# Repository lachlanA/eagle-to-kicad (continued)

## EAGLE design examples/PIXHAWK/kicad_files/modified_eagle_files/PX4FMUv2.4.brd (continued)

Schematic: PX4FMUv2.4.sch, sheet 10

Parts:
C1001: 10u/25V; 0805-CAP; PARTNO CL21A106KAYNNNE
C1002: 10n; 0402-CAP; PARTNO CC0402KRX7R7BB103
C1003: 1u0; 0603-CAP; PARTNO CC0603ZRY5V7BB105
C1004: 10u; 0603-CAP; PARTNO CC0603ZRY5V7BB105
C1005: 0u1F; 0402-CAP; PARTNO CC0402ZRY5V7BB104
C1008: 2u2; 0402-CAP; PARTNO CC0603ZRY5V7BB105
D1001: PMEG2005CT; SOT23-3; PARTNO PMEG2005CT
F1001: 0ZCA0035FF2G; PTC-1206; PARTNO 0ZCA0035FF2G
R1001: 100K; 0402-RES; PARTNO RC0402FR-07100KL
R1002: 10K; 0402-RES; PARTNO RC0402FR-0710KL
U1001: BQ24313; QFN8-DSG; PARTNO BQ24313DSGT
U1002: MIC5332; MLF-8-EPAD; PARTNO MIC5332-SSYMT

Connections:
GND: C1001.P$2 (2), C1002.P$2 (2), C1003.P$2 (2), C1004.P$2 (2), C1005.P$2 (2), C1008.P$2 (2), R1001.P$1 (1), R1002.P$1 (1), U1001.2 (VSS), U1001.5 (!CE), U1001.6 (VBAT), U1001.GND (VSS), U1001.P$2 (VSS), U1001.P$3 (VSS), U1002.2 (GND), U1002.GND; also elsewhere on the board
IO-!RESET: U1002.3 (POR2); also elsewhere on the board
IO-!VDD_SERVO_IN_FAULT: U1001.4 (!FAULT); also elsewhere on the board
IO-VDD_3V3: C1003.P$1 (1), C1004.P$1 (1), U1002.7 (VOUT2); also elsewhere on the board
IO-VDD_5V5: C1001.P$1 (1), C1005.P$1 (1), D1001.3 (CC), U1002.1 (VIN), U1002.4 (EN2); also elsewhere on the board
unnamed: D1001.2 (A2), U1001.8 (OUT)
unnamed: R1001.P$2 (2), U1001.7 (ILIM)
unnamed: D1001.1 (A1), F1001.2
unnamed: C1002.P$1 (1), U1002.6 (CSET)
VDD_3V3_SPEKTRUM: C1008.P$1 (1), U1002.8 (VOUT1); also elsewhere on the board
VDD_3V3_SPEKTRUM_EN: R1002.P$2 (2), U1002.5 (EN1); also elsewhere on the board
VDD_5V_IN: F1001.1; also elsewhere on the board
VDD_SERVO_IN: U1001.1 (IN); also elsewhere on the board

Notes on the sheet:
Dual supply from servo rail and FMU 5V rail
Current limit = 25 / Rilim (current in A, R in kOhms) 100K = 250mA
IO Power Supply
Reset output 1s / uF 10n = 10ms delay from power good to reset de-asserted.
Output voltage limited to 5.5V for input voltages up to 10.5V; output switches off at higher input voltages.

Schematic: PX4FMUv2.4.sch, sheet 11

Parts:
C1101, C1102, C1103: 22u/25V; 0805-CAP; PARTNO CL21A226MAQNNNE
C1104: 100u; 1206-CAP; PARTNO C3216X5R1A107M160AC
C1105, C1106, C1107: 0u1; 0402-CAP; PARTNO CC0402ZRY5V7BB104
C1108, C1109, C1110: 1000p/25V; 0402-CAP; PARTNO GRM1555C1E102JA01D
J601: DF13C-6P-1.25V; PARTNO DF13C-6P-1.25V(20)
L1101, L1102: KNH16C104DA5TS; KYOCERA-KNH16-DA; PARTNO KNH16C104DA5TS
R1101, R1102: 10K/0.1%; 0402-RES; PARTNO ERA-2AEB103X
R1103, R1104: 1M; 0402-RES; PARTNO RC0402FR-071ML
R1105, R1109, R1112: 453K; 0402-RES; PARTNO RMCF0402FT453K
R1106, R1110, R1113: 56K; 0402-RES; PARTNO ERA-2AEB563X
R1107, R1111, R1114: 105K; 0402-RES; PARTNO ERJ-2RKF1053X
R1115: 0R; 0402-RES; PARTNO ERJ-2GE0R00X
RN1101: 1M; EXB28V; PARTNO EXB-28V105JX
U1101: LTC4417; MO-220; PARTNO LTC4417IUF#PBF
U1102, U1103, U1104: NTHD4102PT1G; 1206-8; PARTNO NTHD4102PT1G

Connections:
!VBUS_VALID: RN1101.2 (1), U1101.P$9 (!VALID3); also elsewhere on the board
!VDD_BRICK_VALID: RN1101.4 (1), U1101.P$7 (!VALID1); also elsewhere on the board
!VDD_SERVO_VALID: RN1101.3 (1), U1101.P$8 (!VALID2); also elsewhere on the board
BATT_CURRENT_SENS: R1101.P$1 (1); also elsewhere on the board
BATT_CURRENT_SENS_PROT: J601.3, L1101.P$1, R1104.P$1 (1)
BATT_VOLTAGE_SENS: R1102.P$1 (1); also elsewhere on the board
BATT_VOLTAGE_SENS_PROT: J601.4, L1102.P$1, R1103.P$1 (1)
GND: C1101.P$2 (2), C1102.P$2 (2), C1103.P$2 (2), C1104.P$2 (2), C1105.P$2 (2), C1106.P$2 (2), C1107.P$2 (2), C1108.P$2 (2), C1109.P$2 (2), C1110.P$2 (2), J601.5, J601.6, L1101.P$3, L1101.P$4, L1101.P$5, L1102.P$3, L1102.P$4, L1102.P$5, R1103.P$2 (2), R1104.P$2 (2), R1107.P$2 (2), R1111.P$2 (2), R1114.P$2 (2), R1115.P$1 (1), U1101.P$10 (GND), U1101.P$25 (GND); also elsewhere on the board
unnamed: C1108.P$1 (1), R1105.P$2 (2), R1106.P$1 (1), U1101.P$1 (UV1)
unnamed: R1106.P$2 (2), R1107.P$1 (1), U1101.P$2 (OV1)
unnamed: C1109.P$1 (1), R1109.P$2 (2), R1110.P$1 (1), U1101.P$3 (UV2)
unnamed: R1110.P$2 (2), R1111.P$1 (1), U1101.P$4 (OV2)
unnamed: R1113.P$2 (2), R1114.P$1 (1), U1101.P$6 (OV3)
unnamed: C1110.P$1 (1), R1112.P$2 (2), R1113.P$1 (1), U1101.P$5 (UV3)
unnamed: C1105.P$1 (1), U1101.P$18 (VS1), U1102.P$1 (S), U1102.P$3 (S)
unnamed: L1102.P$2, R1102.P$2 (2)
unnamed: L1101.P$2, R1101.P$2 (2)
unnamed: R1115.P$2 (2), U1101.P$24 (HYS)
unnamed: C1106.P$1 (1), U1101.P$16 (VS2), U1103.P$1 (S), U1103.P$3 (S)
unnamed: C1107.P$1 (1), U1101.P$14 (VS3), U1104.P$1 (S), U1104.P$3 (S)
unnamed: U1101.P$13 (G3), U1104.P$2 (G), U1104.P$4 (G)
unnamed: U1101.P$15 (G2), U1103.P$2 (G), U1103.P$4 (G)
unnamed: U1101.P$17 (G1), U1102.P$2 (G), U1102.P$4 (G)
VBUS: C1103.P$1 (1), R1112.P$1 (1), U1101.P$19 (V3), U1104.P$7 (D), U1104.P$8 (D); also elsewhere on the board
VDD_5V_BRICK: C1101.P$1 (1), J601.1, J601.2, R1105.P$1 (1), U1101.P$21 (V1), U1102.P$7 (D), U1102.P$8 (D); also elsewhere on the board
VDD_5V_IN: C1104.P$1 (1), RN1101.5 (2), RN1101.6 (2), RN1101.7 (2), U1101.P$12 (VOUT), U1102.P$5 (D), U1102.P$6 (D), U1103.P$5 (D), U1103.P$6 (D), U1104.P$5 (D), U1104.P$6 (D); also elsewhere on the board
VDD_SERVO: C1102.P$1 (1), R1109.P$1 (1), U1101.P$20 (V2), U1103.P$7 (D), U1103.P$8 (D); also elsewhere on the board

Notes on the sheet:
Power source selector
Resistors picked so that undervoltage lockout starts at 4.0V and overvoltage lockout at 5.75V. Use 1% or better accuracy!
POWER PATH CONTROLLER: Does enable output if valid for continous 256 ms

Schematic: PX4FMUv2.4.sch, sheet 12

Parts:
!VBUS_VALID1116: PAD.04; PAD.04X.04; PARTNO *
!VDD_BRICK_VALID1116: PAD.04; PAD.04X.04; PARTNO *
!VDD_SERVO_VALID1116: PAD.04; PAD.04X.04; PARTNO *
ADC_PR1116: PAD.04; PAD.04X.04; PARTNO *
CAN_H1116: PAD.04; PAD.04X.04; PARTNO *
CAN_L1116: PAD.04; PAD.04X.04; PARTNO *
FMU-BOOT1101: PAD.04; PAD.04X.04; PARTNO *
GND1116, GND.1116: PAD.04; PAD.04X.04; PARTNO *
IO-BOOT1101: PAD.04; PAD.04X.04; PARTNO *
JP1, JP2: FIDUCIAL1.5X3; FIDUCIAL-1.5X3; PARTNO *
M3_MOUNT1101, M3_MOUNT1102, M3_MOUNT1103, M3_MOUNT1104: MOUNT-HOLE3.1MM; MOUNT-HOLE3.1; PARTNO *
OSHW_LOGO1116: OSHW-LOGOS; OSHW-LOGO-S; PARTNO *
S1RX1116, S1TX1116, S2RX1116, S2TX1116, S3RX1116, S3TX1116, S4RX1116, S4TX1116, S5_RX1116, S5_TX1116: PAD.04; PAD.04X.04; PARTNO *
VBUS1116: PAD.04; PAD.04X.04; PARTNO *
VDDA_3V1101: PAD.04; PAD.04X.04; PARTNO *
VDD_3V1101, VDD_5V_BRICK1116, VDD_5V_IN1116: PAD.04; PAD.04X.04; PARTNO *
VDD_SERVO1116: PAD.04; PAD.04X.04; PARTNO *
VP_0, VP_1, VP_2, VP_3, VP_33, VP_34, VP_35, VP_41, VP_42, VP_43, VP_51, VP_52, VP_53, VP_54, VP_55, VP_56, VP_57, VP_58, VP_59, VP_60, VP_61: VPDEV0; VPAC0
VP_4, VP_5, VP_6, VP_7, VP_8, VP_9, VP_10, VP_11, VP_12, VP_13, VP_14, VP_15, VP_16, VP_17, VP_18, VP_19, VP_20, VP_21, VP_22, VP_23, VP_24, VP_25, VP_26, VP_27, VP_28, VP_29, VP_30, VP_31, VP_32, VP_36, VP_37, VP_39, VP_40, VP_44, VP_45, VP_46, VP_47, VP_48, VP_49, VP_50: VPDEV1; VPAC1
VP_38: VPDEV2; VPAC2

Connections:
!VBUS_VALID: !VBUS_VALID1116.P$1; also elsewhere on the board
!VDD_BRICK_VALID: !VDD_BRICK_VALID1116.P$1; also elsewhere on the board
!VDD_SERVO_VALID: !VDD_SERVO_VALID1116.P$1; also elsewhere on the board
CAN_H: CAN_H1116.P$1; also elsewhere on the board
CAN_L: CAN_L1116.P$1; also elsewhere on the board
FMU-BOOT0: FMU-BOOT1101.P$1; also elsewhere on the board
FMU-VDD_3V3: VDD_3V1101.P$1; also elsewhere on the board
GND: GND1116.P$1, GND.1116.P$1, VP_0.VP, VP_1.VP, VP_2.VP, VP_3.VP, VP_4.VP, VP_5.VP, VP_6.VP, VP_7.VP, VP_8.VP, VP_9.VP, VP_10.VP, VP_11.VP, VP_12.VP, VP_13.VP, VP_14.VP, VP_15.VP, VP_16.VP, VP_17.VP, VP_18.VP, VP_19.VP, VP_20.VP, VP_21.VP, VP_22.VP, VP_23.VP, VP_24.VP, VP_25.VP, VP_26.VP, VP_27.VP, VP_28.VP, VP_29.VP, VP_30.VP; also elsewhere on the board
IO-BOOT0: IO-BOOT1101.P$1; also elsewhere on the board
IO-VDD_3V3: VP_31.VP, VP_32.VP; also elsewhere on the board
PRESSURE_SENS_IN: ADC_PR1116.P$1; also elsewhere on the board
SERIAL1_RX: S1RX1116.P$1; also elsewhere on the board
SERIAL1_TX: S1TX1116.P$1; also elsewhere on the board
SERIAL2_RX: S2RX1116.P$1; also elsewhere on the board
SERIAL2_TX: S2TX1116.P$1; also elsewhere on the board
SERIAL3_RX: S3RX1116.P$1; also elsewhere on the board
SERIAL3_TX: S3TX1116.P$1; also elsewhere on the board
SERIAL4_RX: S4RX1116.P$1; also elsewhere on the board
SERIAL4_TX: S4TX1116.P$1; also elsewhere on the board
SERIAL5_RX: S5_RX1116.P$1; also elsewhere on the board
SERIAL5_TX: S5_TX1116.P$1; also elsewhere on the board
VBUS: VBUS1116.P$1, VP_33.VP, VP_34.VP, VP_35.VP; also elsewhere on the board
VDD_3V3_SENSORS: VDDA_3V1101.P$1, VP_36.VP, VP_37.VP; also elsewhere on the board
VDD_5V_BRICK: VDD_5V_BRICK1116.P$1, VP_38.VP, VP_39.VP, VP_40.VP; also elsewhere on the board
VDD_5V_IN: VDD_5V_IN1116.P$1, VP_41.VP, VP_42.VP, VP_43.VP, VP_44.VP, VP_45.VP, VP_46.VP, VP_47.VP, VP_48.VP, VP_49.VP, VP_50.VP, VP_51.VP, VP_52.VP, VP_53.VP; also elsewhere on the board
VDD_5V_PERIPH: VP_54.VP, VP_55.VP, VP_56.VP, VP_57.VP, VP_58.VP; also elsewhere on the board
VDD_SERVO: VDD_SERVO1116.P$1, VP_59.VP, VP_60.VP, VP_61.VP; also elsewhere on the board

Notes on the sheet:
Mounting holes to suit M3 fastener
and Richco R908 series spacer.
Use R908-5 spacers to stack with
other PX4 series boards (7.95 mm).
Production Testing Pads
Test and Fiducials
Minimum drill: 0.3 mm
Minimum trace width (use mm for traces): 0.15 mm
Minimum copper distance (all signals): 0.15 mm
Dimension / hole minimum distance: 0.2 mm
Layout grid: 4 mil, part grid: 4 mil. Dimensions / hole positions: 0.5 mm
Board: FR4 black, 1.0 mm. Solder stop on vias < 0.6 mm.
Signoff rules: Footprint checked, pinmap checked, schematic checked, cross-references to other pages checked.
Routing: 1: general/escape 2: ground 3: horizontal 4: vertical 5: power 6: general/escape
Fiducials for machine vision alignment.
Parts: Resistors: 0402 / 1% unless specified otherwise Capacitors: 0402 to 1206, ceramic, voltage rating: 10V unless specified

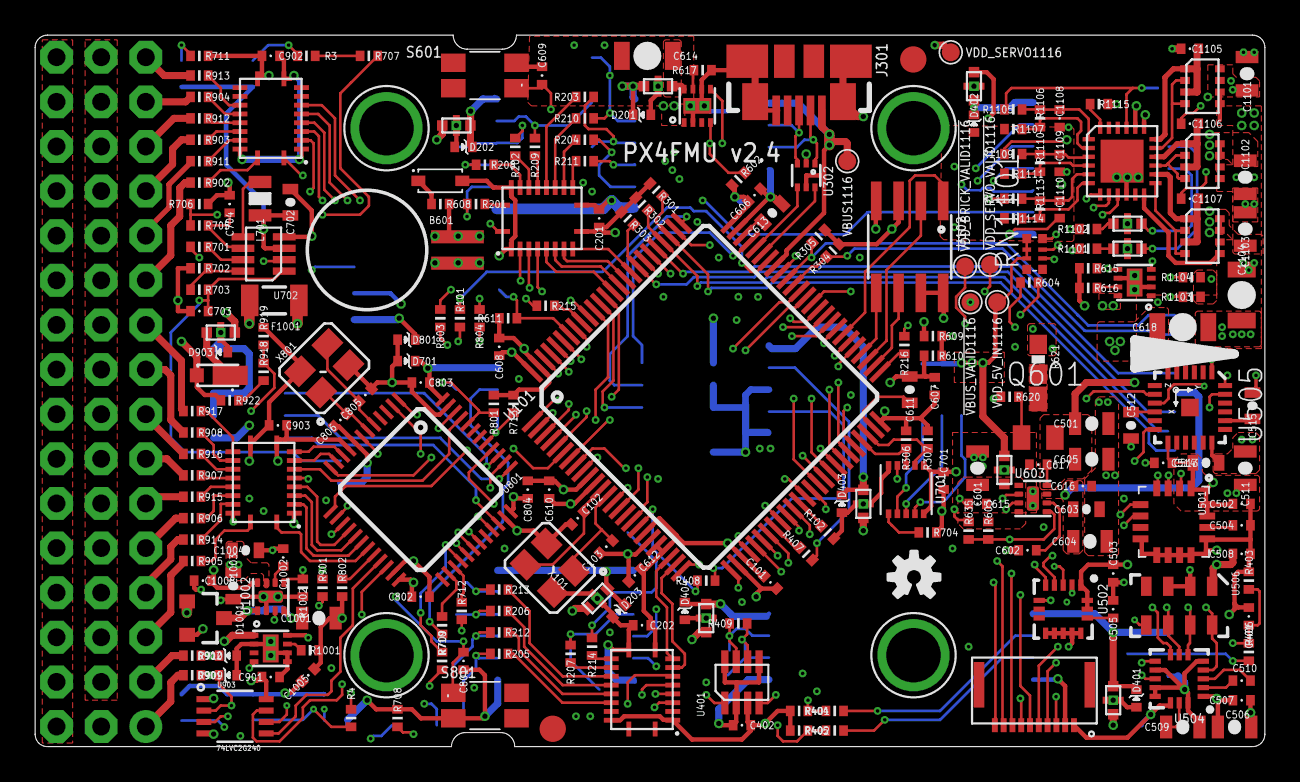
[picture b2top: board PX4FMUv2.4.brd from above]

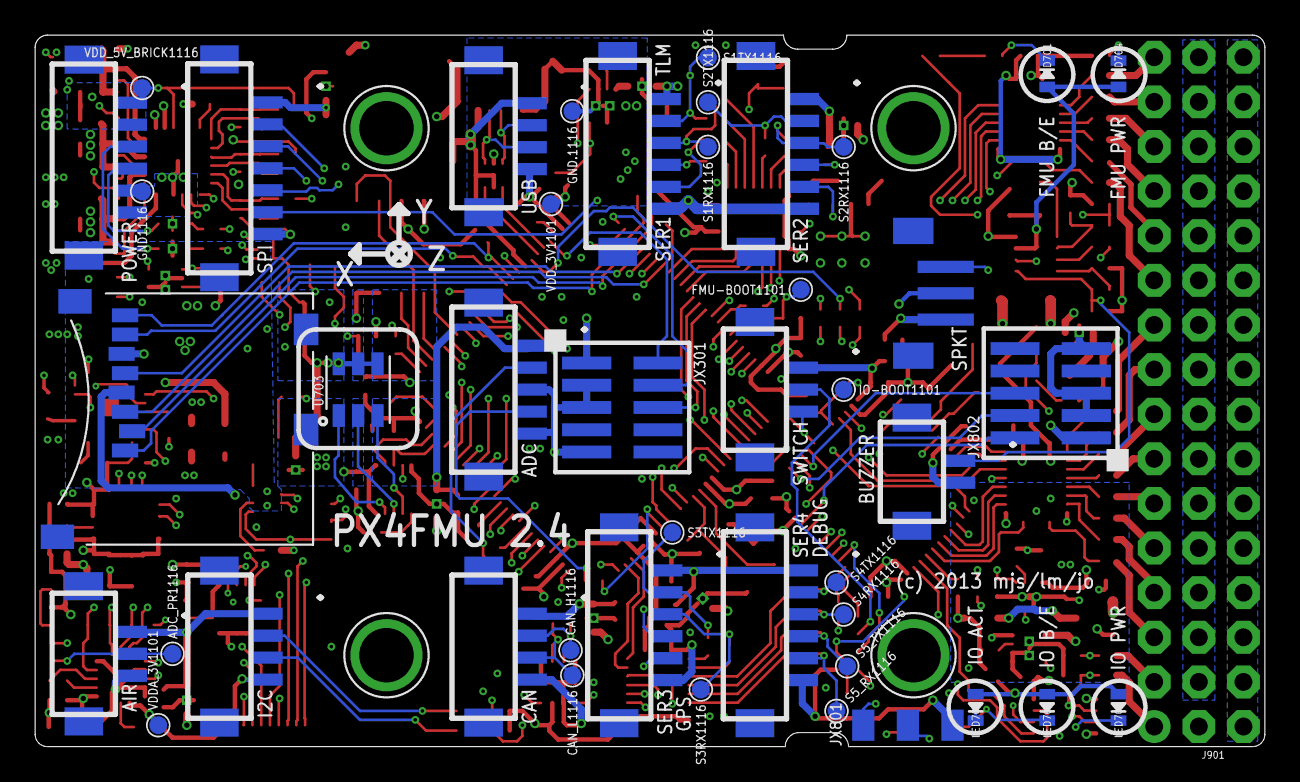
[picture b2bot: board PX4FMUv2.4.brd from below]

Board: 6 copper layers, 70.0 x 40.5 mm, 354 parts (45 on the bottom side), 262 nets.

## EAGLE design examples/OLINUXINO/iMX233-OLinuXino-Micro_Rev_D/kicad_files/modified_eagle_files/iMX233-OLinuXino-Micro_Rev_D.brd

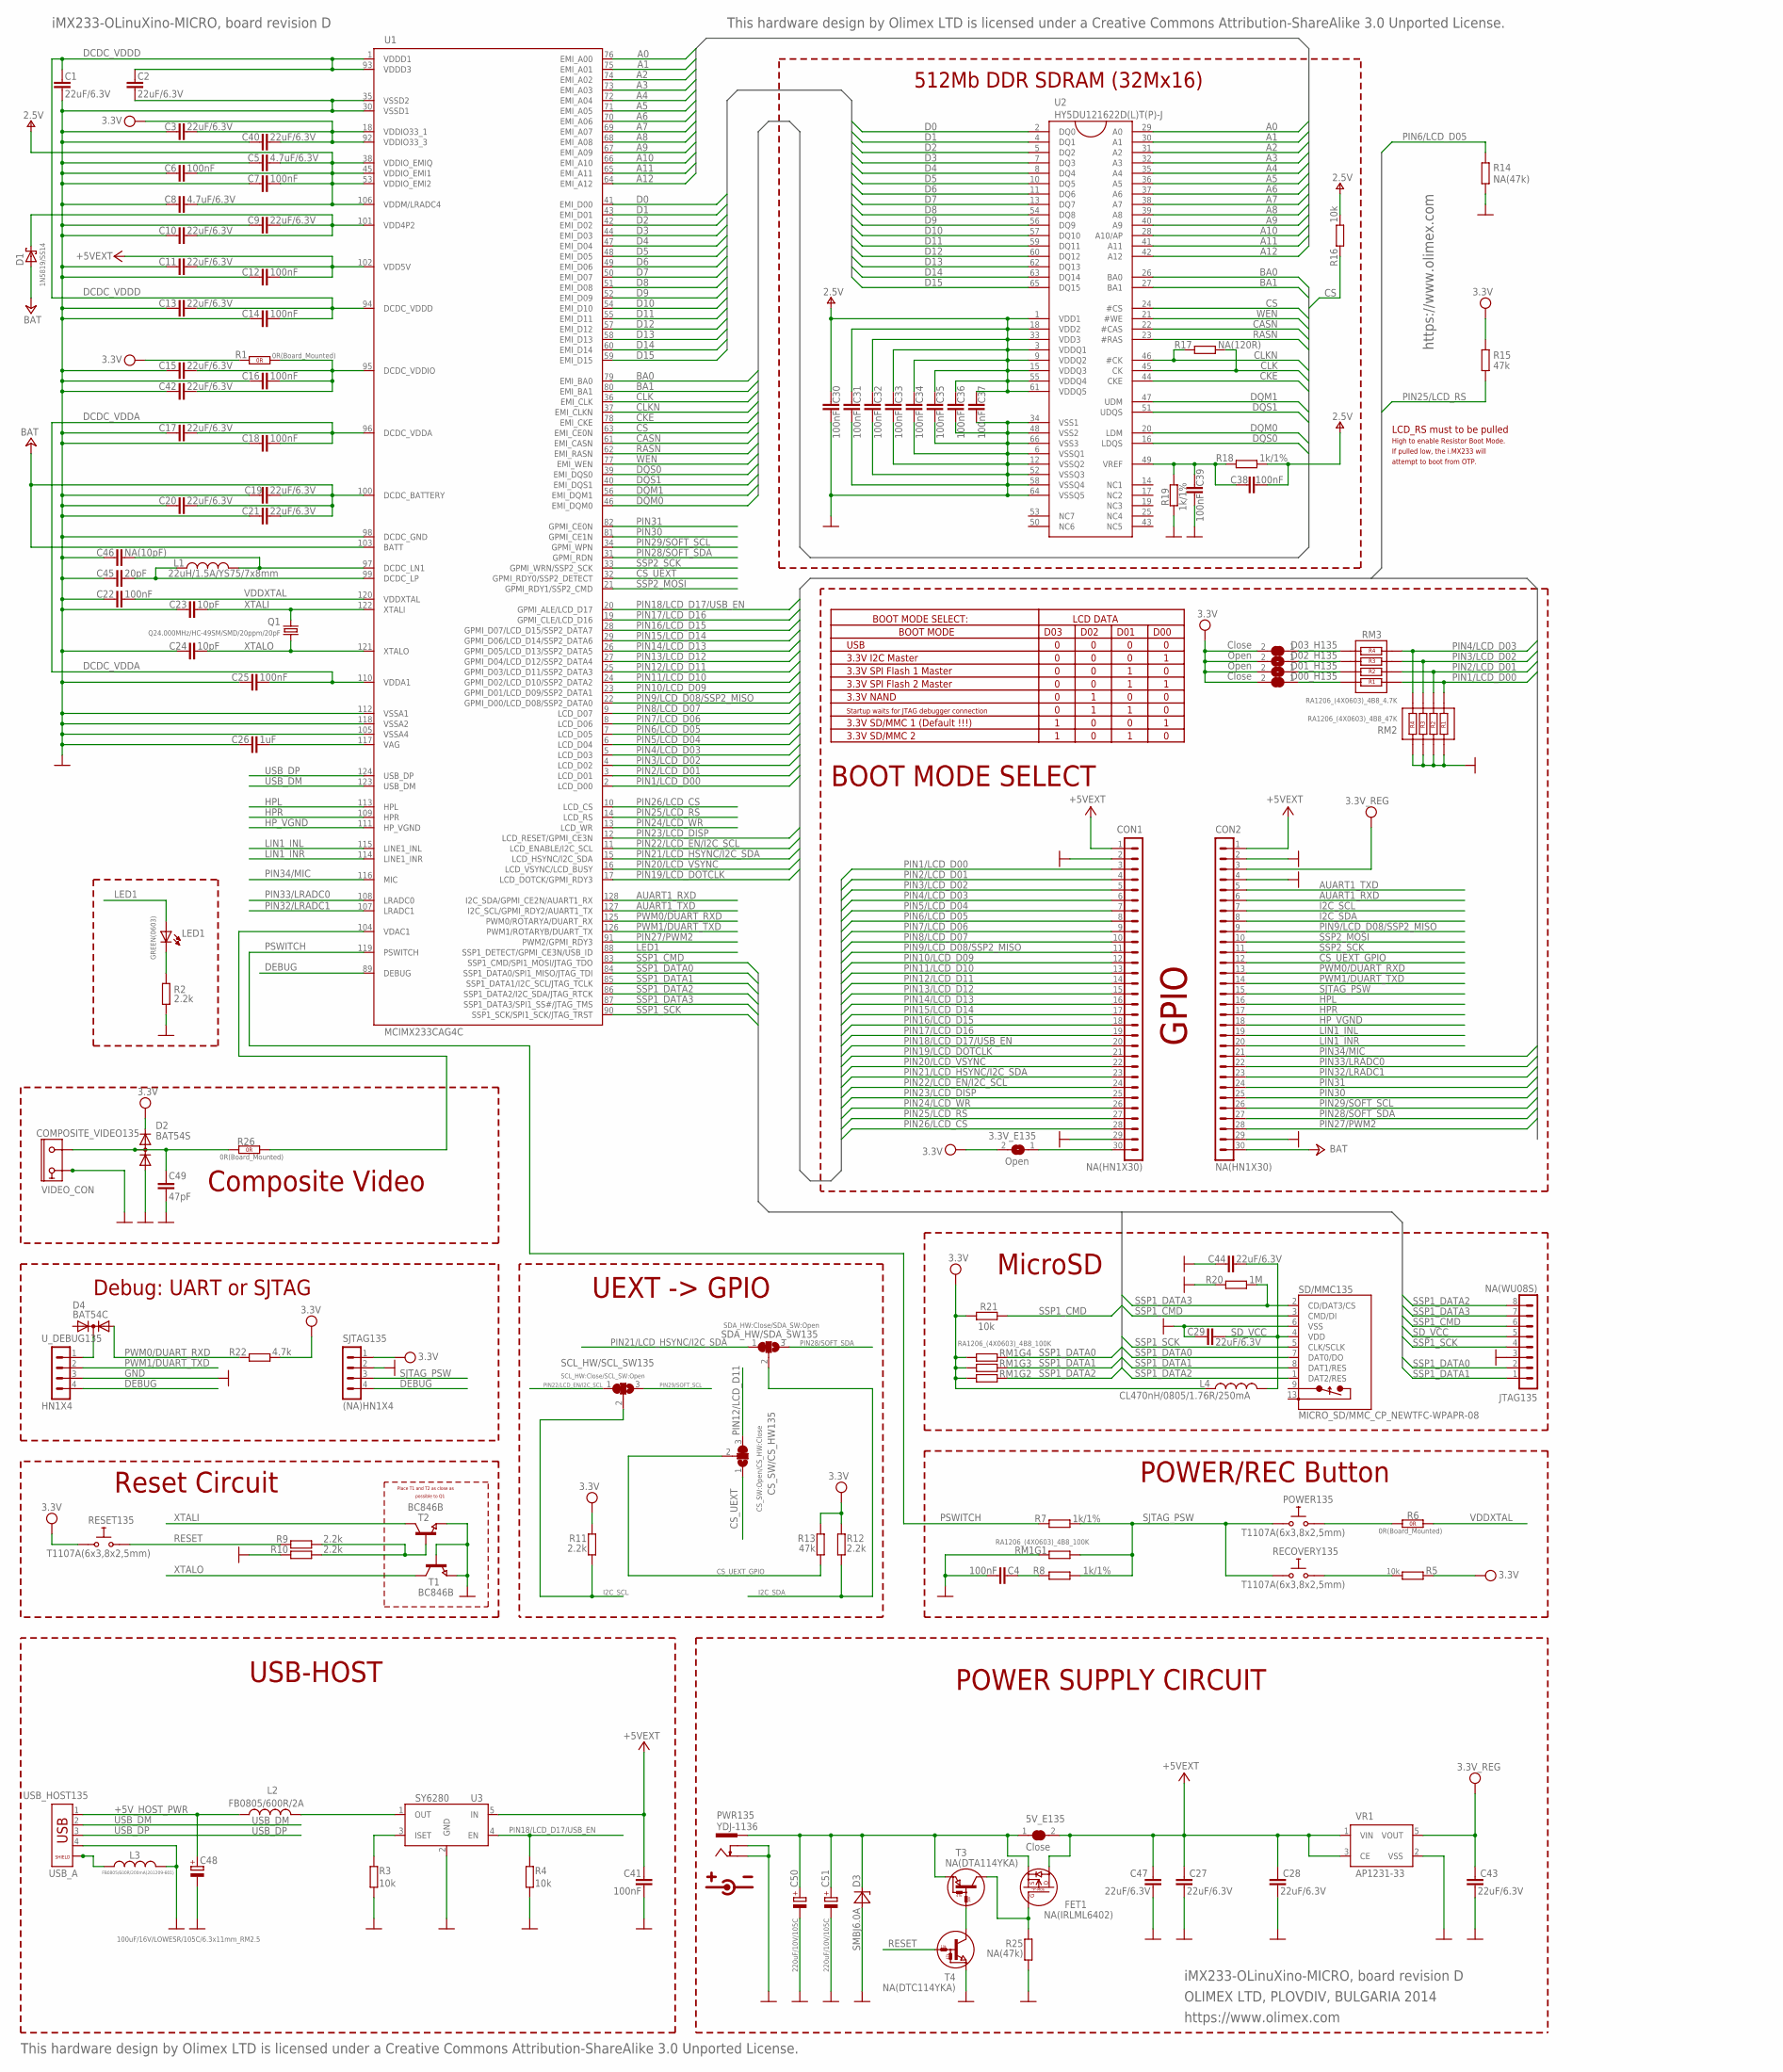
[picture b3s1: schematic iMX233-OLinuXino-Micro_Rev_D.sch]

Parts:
3.3V_E135: Open; SJ_1_SMALLER
5V_E135: Close; SJ-CLOSE
C1, C2, C9, C10, C11, C13, C15, C17, C19, C20, C21, C27, C28, C29, C40, C42, C43, C44, C47: 22uF/6.3V; C0603_DWS
C3: 22uF/6.3V; C1206
C4, C6, C7, C12, C14, C16, C18, C22, C25, C30, C31, C32, C33, C34, C35, C36, C37, C38, C39, C41: 100nF; C0603_DWS
C5, C8: 4.7uF/6.3V; C0603_DWS
C23, C24: 10pF; C0603_DWS
C26: 1uF; C0603_DWS
C45: 20pF; C0603_DWS
C46: NA(10pF); C0603_DWS
C48: 100uF/16V/LOWESR/105C/6.3x11mm_RM2.5; E2,5-6,3
C49: 47pF; C0603_DWS
C50, C51: 220uF/10V/105C; E2,5-6,3
COMPOSITE_VIDEO135: VIDEO_CON; VIDEO_CINCH
CON1, CON2: NA(HN1X30); HN1X30
CS_SW/CS_HW135: CS_SW:Open/CS_HW:Close; SJ_2_SMALL
D00_H135, D03_H135: Close; SJ_1_SMALLER
D1: 1N5819/SS14; MLL-41
D01_H135, D02_H135: Open; SJ_1_SMALLER
D2: BAT54S; SOT23C(BAT54S)
D3: SMBJ6.0A; DO214AA
D4: BAT54C; SOT23C
FET1: NA(IRLML6402); SOT23
JTAG135: NA(WU08S); WU08S
L1: 22uH/1.5A/YS75/7x8mm; L7078
L2: FB0805/600R/2A; L0805_5MIL_DWS
L3: FB0805/600R/200mA(201209-601); L0805_5MIL_DWS
L4: CL470nH/0805/1.76R/250mA; L0805_5MIL_DWS
LED1: GREEN(0603); LED-0603
POWER135: T1107A(6x3,8x2,5mm); SW-TAKT_6X3.5_SMD
PWR135: YDJ-1136; PWR_JACK_UNI_MILLING
Q1: Q24.000MHz/HC-49SM/SMD/20ppm/20pF; HC49/SMD2_THIN
R1, R6, R26: 0R(Board_Mounted); 0603_0R
R2, R9, R10, R11, R12: 2.2k; R0603_5MIL_DWS
R3, R4, R5, R16, R21: 10k; R0603_5MIL_DWS
R7, R8, R18, R19: 1k/1%; R0603_5MIL_DWS
R13, R15: 47k; R0603_5MIL_DWS
R14, R25: NA(47k); R0603_5MIL_DWS
R17: NA(120R); R0603_5MIL_DWS
R20: 1M; R0603_5MIL_DWS
R22: 4.7k; R0603_5MIL_DWS
RECOVERY135: T1107A(6x3,8x2,5mm); SW-TAKT_6X3.5_SMD
RESET135: T1107A(6x3,8x2,5mm); SW-TAKT_6X3.5_SMD
RM1: RA1206_(4X0603)_4B8_100K; R_MATRIX_4
RM2: RA1206_(4X0603)_4B8_47K; R_MATRIX_4
RM3: RA1206_(4X0603)_4B8_4.7K; R_MATRIX_4
SCL_HW/SCL_SW135: SCL_HW:Close/SCL_SW:Open; SJ_2_SMALL
SD/MMC135: MICRO_SD/MMC_CP_NEWTFC-WPAPR-08; TFC-WPAPR-08
SDA_HW/SDA_SW135: SDA_HW:Close/SDA_SW:Open; SJ_2_SMALL
SJTAG135: (NA)HN1X4; HN1X4
T1, T2: BC846B; SOT23
T3: NA(DTA114YKA); SOT-23
T4: NA(DTC114YKA); SOT-23
U1: MCIMX233CAG4C; TQFP128LD
U2: HY5DU121622D(L)T(P)-J; 66TSOP-II
U3: SY6280; SOT23-5
USB_HOST135: USB_A; USB_PN87520_HOST_PTH
U_DEBUG135: HN1X4
VR1: AP1231-33; SOT-23-5

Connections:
+5V: 5V_E135.2, C11.2, C12.2, C27.1, C28.1, C41.1, C47.1, CON1.1, CON2.1, FET1.3 (D), U1.102 (VDD5V), U3.5 (IN), VR1.1 (VIN), VR1.3 (CE)
+5V_HOST_PWR: C48.+, L2.1, USB_HOST135.1
+24V: C19.2, C20.2, C21.2, CON2.30, D1.A, U1.100 (DCDC_BATTERY), U1.103 (BATT)
A0: U1.76 (EMI_A00), U2.29 (A0)
A1: U1.75 (EMI_A01), U2.30 (A1)
A2: U1.74 (EMI_A02), U2.31 (A2)
A3: U1.73 (EMI_A03), U2.32 (A3)
A4: U1.72 (EMI_A04), U2.35 (A4)
A5: U1.71 (EMI_A05), U2.36 (A5)
A6: U1.70 (EMI_A06), U2.37 (A6)
A7: U1.69 (EMI_A07), U2.38 (A7)
A8: U1.68 (EMI_A08), U2.39 (A8)
A9: U1.67 (EMI_A09), U2.40 (A9)
A10: U1.66 (EMI_A10), U2.28 (A10/AP)
A11: U1.65 (EMI_A11), U2.41 (A11)
A12: U1.64 (EMI_A12), U2.42 (A12)
AUART1_RXD: CON2.6, U1.128 (I2C_SDA/GPMI_CE2N/AUART1_RX)
AUART1_TXD: CON2.5, U1.127 (I2C_SCL/GPMI_RDY2/AUART1_TX)
BA0: U1.79 (EMI_BA0), U2.26 (BA0)
BA1: U1.80 (EMI_BA1), U2.27 (BA1)
CASN: U1.61 (EMI_CASN), U2.22 (#CAS)
CKE: U1.78 (EMI_CKE), U2.44 (CKE)
CLK: R17.2, U1.36 (EMI_CLK), U2.45 (CK)
CLKN: R17.1, U1.37 (EMI_CLKN), U2.46 (#CK)
CS: R16.1, U1.63 (EMI_CE0N), U2.24 (#CS)
CS_UEXT: CS_SW/CS_HW135.1, U1.32 (GPMI_RDY0/SSP2_DETECT)
CS_UEXT_GPIO: CON2.12, CS_SW/CS_HW135.2, R13.1
D0: U1.41 (EMI_D00), U2.2 (DQ0)
D1: U1.43 (EMI_D01), U2.4 (DQ1)
D2: U1.42 (EMI_D02), U2.5 (DQ2)
D3: U1.44 (EMI_D03), U2.7 (DQ3)
D4: U1.47 (EMI_D04), U2.8 (DQ4)
D5: U1.48 (EMI_D05), U2.10 (DQ5)
D6: U1.49 (EMI_D06), U2.11 (DQ6)
D7: U1.50 (EMI_D07), U2.13 (DQ7)
D8: U1.51 (EMI_D08), U2.54 (DQ8)
D9: U1.52 (EMI_D09), U2.56 (DQ9)
D10: U1.54 (EMI_D10), U2.57 (DQ10)
D11: U1.55 (EMI_D11), U2.59 (DQ11)
D12: U1.57 (EMI_D12), U2.60 (DQ12)
D13: U1.58 (EMI_D13), U2.62 (DQ13)
D14: U1.60 (EMI_D14), U2.63 (DQ14)
D15: U1.59 (EMI_D15), U2.65 (DQ15)
DCDC_VDDA: C17.2, C18.2, C25.2, U1.96 (DCDC_VDDA), U1.110 (VDDA1)
DCDC_VDDD: C1.2, C2.2, C13.2, C14.2, U1.1 (VDDD1), U1.93 (VDDD3), U1.94 (DCDC_VDDD)
DCDC_VDDIO: C15.2, C16.2, C42.2, R1.2 (1.2), U1.95 (DCDC_VDDIO)
DEBUG: SJTAG135.4, U1.89 (DEBUG), U_DEBUG135.4
DQM0: U1.46 (EMI_DQM0), U2.20 (LDM)
DQM1: U1.56 (EMI_DQM1), U2.47 (UDM)
DQS0: U1.39 (EMI_DQS0), U2.16 (LDQS)
DQS1: U1.40 (EMI_DQS1), U2.51 (UDQS)
GND: C1.1, C2.1, C3.1, C4.2, C5.1, C6.1, C7.1, C8.1, C9.1, C10.1, C11.1, C12.1, C13.1, C14.1, C15.1, C16.1, C17.1, C18.1, C19.1, C20.1, C21.1, C22.1, C23.1, C24.1, C25.1, C26.1, C27.2, C28.2, C29.1, C30.1, C31.1, C32.1, C33.1, C34.1, C35.1, C36.1, C37.1, C39.1, C40.1, C41.2, C42.1, C43.2, C44.1, C45.1, C46.1, C47.2, C48.-, C49.2, C50.-, C51.-, COMPOSITE_VIDEO135.GND1 (GND), COMPOSITE_VIDEO135.GND1A (GND), COMPOSITE_VIDEO135.GND1B (GND), COMPOSITE_VIDEO135.GND1C (GND), COMPOSITE_VIDEO135.GND1D (GND), COMPOSITE_VIDEO135.GND1E (GND), COMPOSITE_VIDEO135.GND2 (GND), COMPOSITE_VIDEO135.GND3 (GND), COMPOSITE_VIDEO135.GND3C (GND), COMPOSITE_VIDEO135.GND3D (GND), COMPOSITE_VIDEO135.GND3E (GND), COMPOSITE_VIDEO135.GNG3A (GND), COMPOSITE_VIDEO135.GNG3B (GND), CON1.2, CON1.29, CON2.2, CON2.4, CON2.29, D2.1 (A), D3.A, JTAG135.3, L3.1, PWR135.-, PWR135.--, R2.1, R3.1, R4.1, R10.2, R14.1, R19.1, R20.2, R25.1, RM1.1.1 (1), RM2.1.2, RM2.2.2, RM2.3.2, RM2.4.2, SD/MMC135.6 (VSS), SJTAG135.2, T1.1 (B), T1.2 (E), T2.2 (E), T4.2 (E), U1.30 (VSSD1), U1.35 (VSSD2), U1.98 (DCDC_GND), U1.105 (VSSA4), U1.112 (VSSA1), U1.118 (VSSA2), U2.6 (VSSQ1), U2.12 (VSSQ2), U2.34 (VSS1), U2.48 (VSS2), U2.52 (VSSQ3), U2.58 (VSSQ4), U2.64 (VSSQ5), U2.66 (VSS3), U3.2 (GND), USB_HOST135.4, U_DEBUG135.3, VR1.2 (VSS)
HPL: CON2.16, U1.113 (HPL)
HPR: CON2.17, U1.109 (HPR)
HP_VGND: CON2.18, U1.111 (HP_VGND)
I2C_SCL: CON2.7, R11.1, SCL_HW/SCL_SW135.2
I2C_SDA: CON2.8, R12.1, SDA_HW/SDA_SW135.2
LED1: LED1.A, U1.88 (SSP1_DETECT/GPMI_CE3N/USB_ID)
LIN1_INL: CON2.19, U1.115 (LINE1_INL)
LIN1_INR: CON2.20, U1.114 (LINE1_INR)
unnamed: POWER135.P$1 (0), R6.1 (1.1)
unnamed: 3.3V_E135.1, CON1.30
unnamed: 5V_E135.1, C50.+, C51.+, D3.C, FET1.2 (S), PWR135.+, T3.2 (E)
unnamed: C49.1, COMPOSITE_VIDEO135.IO, D2.3 (AK), R26.2 (1.2)
unnamed: L2.2, U3.1 (OUT)
unnamed: R3.2, U3.3 (ISET)
unnamed: C38.2, C39.2, R18.1, R19.2, U2.49 (VREF)
unnamed: R5.1, RECOVERY135.P$1 (0)
unnamed: D4.3 (K), U_DEBUG135.1
unnamed: FET1.1 (G), R25.2, T3.3 (C)
unnamed: T3.1 (B), T4.3 (C)
unnamed: C46.2, L1.2, U1.97 (DCDC_LN1)
unnamed: C45.2, L1.1, U1.99 (DCDC_LP)
unnamed: C26.2, U1.117 (VAG)
unnamed: C4.1, R8.1
unnamed: LED1.C, R2.2
unnamed: R9.1, R10.1, T2.1 (B)
unnamed: D03_H135.1, RM3.4.1
unnamed: D02_H135.1, RM3.3.1
unnamed: D01_H135.1, RM3.2.1
unnamed: D00_H135.1, RM3.1.1
unnamed: L3.2, USB_HOST135.P$1 (5), USB_HOST135.P$2 (6)
PIN1/LCD_D00: CON1.3, RM2.1.1, RM3.1.2, U1.2 (LCD_D00)
PIN2/LCD_D01: CON1.4, RM2.2.1, RM3.2.2, U1.3 (LCD_D01)
PIN3/LCD_D02: CON1.5, RM2.3.1, RM3.3.2, U1.4 (LCD_D02)
PIN4/LCD_D03: CON1.6, RM2.4.1, RM3.4.2, U1.5 (LCD_D03)
PIN5/LCD_D04: CON1.7, U1.6 (LCD_D04)
PIN6/LCD_D05: CON1.8, R14.2, U1.7 (LCD_D05)
PIN7/LCD_D06: CON1.9, U1.8 (LCD_D06)
PIN8/LCD_D07: CON1.10, U1.9 (LCD_D07)
PIN9/LCD_D08/SSP2_MISO: CON1.11, CON2.9, U1.22 (GPMI_D00/LCD_D08/SSP2_DATA0)
PIN10/LCD_D09: CON1.12, U1.23 (GPMI_D01/LCD_D09/SSP2_DATA1)
PIN11/LCD_D10: CON1.13, U1.24 (GPMI_D02/LCD_D10/SSP2_DATA2)
PIN12/LCD_D11: CON1.14, CS_SW/CS_HW135.3, U1.25 (GPMI_D03/LCD_D11/SSP2_DATA3)
PIN13/LCD_D12: CON1.15, U1.27 (GPMI_D04/LCD_D12/SSP2_DATA4)
PIN14/LCD_D13: CON1.16, U1.26 (GPMI_D05/LCD_D13/SSP2_DATA5)
PIN15/LCD_D14: CON1.17, U1.29 (GPMI_D06/LCD_D14/SSP2_DATA6)
PIN16/LCD_D15: CON1.18, U1.28 (GPMI_D07/LCD_D15/SSP2_DATA7)
PIN17/LCD_D16: CON1.19, U1.19 (GPMI_CLE/LCD_D16)
PIN18/LCD_D17/USB_EN: CON1.20, R4.2, U1.20 (GPMI_ALE/LCD_D17), U3.4 (EN)
PIN19/LCD_DOTCLK: CON1.21, U1.17 (LCD_DOTCK/GPMI_RDY3)
PIN20/LCD_VSYNC: CON1.22, U1.16 (LCD_VSYNC/LCD_BUSY)
PIN21/LCD_HSYNC/I2C_SDA: CON1.23, SDA_HW/SDA_SW135.1, U1.15 (LCD_HSYNC/I2C_SDA)
PIN22/LCD_EN/I2C_SCL: CON1.24, SCL_HW/SCL_SW135.1, U1.11 (LCD_ENABLE/I2C_SCL)
PIN23/LCD_DISP: CON1.25, U1.12 (LCD_RESET/GPMI_CE3N)
PIN24/LCD_WR: CON1.26, U1.13 (LCD_WR)
PIN25/LCD_RS: CON1.27, R15.2, U1.14 (LCD_RS)
PIN26/LCD_CS: CON1.28, U1.10 (LCD_CS)
PIN27/PWM2: CON2.28, U1.91 (PWM2/GPMI_RDY3)
PIN28/SOFT_SDA: CON2.27, SDA_HW/SDA_SW135.3, U1.31 (GPMI_RDN)
PIN29/SOFT_SCL: CON2.26, SCL_HW/SCL_SW135.3, U1.34 (GPMI_WPN)
PIN30: CON2.25, U1.81 (GPMI_CE1N)
PIN31: CON2.24, U1.82 (GPMI_CE0N)
PIN32/LRADC1: CON2.23, U1.107 (LRADC1)
PIN33/LRADC0: CON2.22, U1.108 (LRADC0)
PIN34/MIC: CON2.21, U1.116 (MIC)
PSWITCH: R7.1, U1.119 (PSWITCH)
PWM0/DUART_RXD: CON2.13, D4.2 (A2), R22.2, U1.125 (PWM0/ROTARYA/DUART_RX)
PWM1/DUART_TXD: CON2.14, U1.126 (PWM1/ROTARYB/DUART_TX), U_DEBUG135.2
RASN: U1.62 (EMI_RASN), U2.23 (#RAS)
RESET: R9.2, RESET135.P$1 (0), T4.1 (B)
SD_VCC: C29.2, C44.2, JTAG135.5, L4.2, SD/MMC135.4 (VDD)
SJTAG_PSW: CON2.15, POWER135.P$2 (1), R7.2, R8.2, RECOVERY135.P$2 (1), RM1.1.2 (2), SJTAG135.3
SSP1_CMD: JTAG135.6, R21.1, SD/MMC135.3 (CMD/DI), U1.83 (SSP1_CMD/SPI1_MOSI/JTAG_TDO)
SSP1_DATA0: JTAG135.2, RM1.4.1 (1), SD/MMC135.7 (DAT0/DO), U1.84 (SSP1_DATA0/SPI1_MISO/JTAG_TDI)
SSP1_DATA1: JTAG135.1, RM1.3.1 (1), SD/MMC135.8 (DAT1/RES), U1.85 (SSP1_DATA1/I2C_SCL/JTAG_TCLK)
SSP1_DATA2: JTAG135.8, RM1.2.1 (1), SD/MMC135.1 (DAT2/RES), U1.86 (SSP1_DATA2/I2C_SDA/JTAG_RTCK)
SSP1_DATA3: JTAG135.7, R20.1, SD/MMC135.2 (CD/DAT3/CS), U1.87 (SSP1_DATA3/SPI1_SS#/JTAG_TMS)
SSP1_SCK: JTAG135.4, SD/MMC135.5 (CLK/SCLK), U1.90 (SSP1_SCK/SPI1_SCK/JTAG_TRST)
SSP2_MOSI: CON2.10, U1.21 (GPMI_RDY1/SSP2_CMD)
SSP2_SCK: CON2.11, U1.33 (GPMI_WRN/SSP2_SCK)
USB_DM: U1.123 (USB_DM), USB_HOST135.2
USB_DP: U1.124 (USB_DP), USB_HOST135.3
V+: C5.2, C6.2, C7.2, C8.2, C30.2, C31.2, C32.2, C33.2, C34.2, C35.2, C36.2, C37.2, C38.1, R16.2, R18.2, U1.38 (VDDIO_EMIQ), U1.45 (VDDIO_EMI1), U1.53 (VDDIO_EMI2), U1.106 (VDDM/LRADC4), U2.1 (VDD1), U2.3 (VDDQ1), U2.9 (VDDQ2), U2.15 (VDDQ3), U2.18 (VDD2), U2.33 (VDD3), U2.55 (VDDQ4), U2.61 (VDDQ5)
VCC: 3.3V_E135.2, C3.2, C40.2, D00_H135.2, D01_H135.2, D2.2 (K), D02_H135.2, D03_H135.2, L4.1, R1.1 (1.1), R5.2, R11.2, R12.2, R13.2, R15.1, R21.2, R22.1, RESET135.P$2 (1), RM1.2.2 (2), RM1.3.2 (2), RM1.4.2 (2), SJTAG135.1, U1.18 (VDDIO33_1), U1.92 (VDDIO33_3)
VDAC1: R26.1 (1.1), U1.104 (VDAC1)
VDD4P2: C9.2, C10.2, D1.K (C), U1.101 (VDD4P2)
VDDXTAL: C22.2, R6.2 (1.2), U1.120 (VDDXTAL)
VPP: C43.1, CON2.3, VR1.5 (VOUT)
WEN: U1.77 (EMI_WEN), U2.21 (#WE)
XTALI: C23.2, Q1.2, T2.3 (C), U1.122 (XTALI)
XTALO: C24.2, Q1.1, T1.3 (C), U1.121 (XTALO)

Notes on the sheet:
POWER SUPPLY CIRCUIT
Place T1 and T2 as close as
possible to Q1
Reset Circuit
512Mb DDR SDRAM (32Mx16)
MicroSD
Composite Video
POWER/REC Button
BOOT MODE SELECT
UEXT -> GPIO
BOOT MODE SELECT:
LCD DATA
BOOT MODE
D03
D02
D01
D00
USB
3.3V I2C Master
3.3V SPI Flash 1 Master
3.3V SPI Flash 2 Master
3.3V NAND
Startup waits for JTAG debugger connection
3.3V SD/MMC 1 (Default !!!)
3.3V SD/MMC 2
LCD_RS must to be pulled
High to enable Resistor Boot Mode.
If pulled low, the i.MX233 will
attempt to boot from OTP.
GPIO
Debug: UART or SJTAG
USB-HOST
iMX233-OLinuXino-MICRO, board revision D
OLIMEX LTD, PLOVDIV, BULGARIA 2014
https://www.olimex.com
This hardware design by Olimex LTD is licensed under a Creative Commons Attribution-ShareAlike 3.0 Unported License.

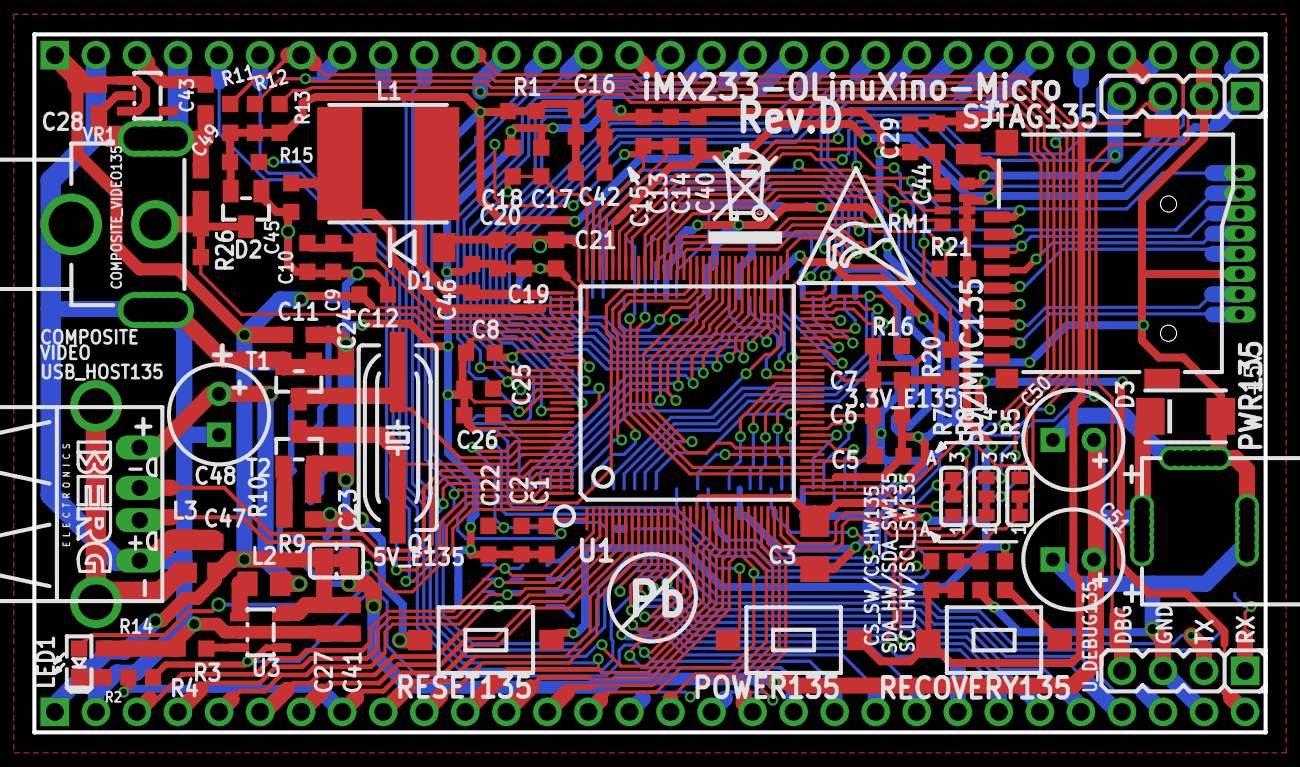
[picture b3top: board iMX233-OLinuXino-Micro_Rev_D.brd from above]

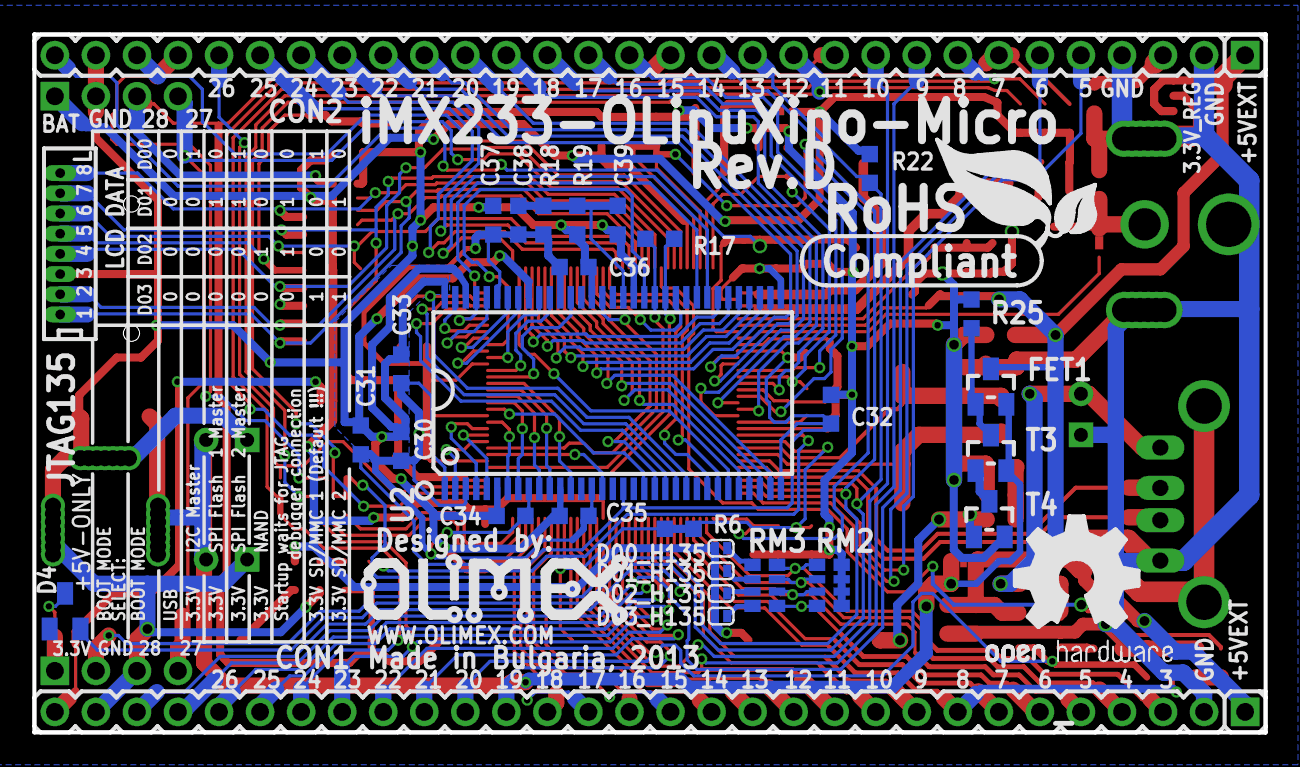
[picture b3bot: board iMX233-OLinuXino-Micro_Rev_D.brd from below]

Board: 4 copper layers, 76.2 x 43.2 mm, 124 parts (33 on the bottom side), 142 nets.

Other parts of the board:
U$5: LOGO-OPENHARDWARE_8X8
U$8: OLIMEX1_V
U$9: PB
U$10: ESD_SYMBOL
U$11: RECYCLE_BIN1/8
U$12: ROHS
